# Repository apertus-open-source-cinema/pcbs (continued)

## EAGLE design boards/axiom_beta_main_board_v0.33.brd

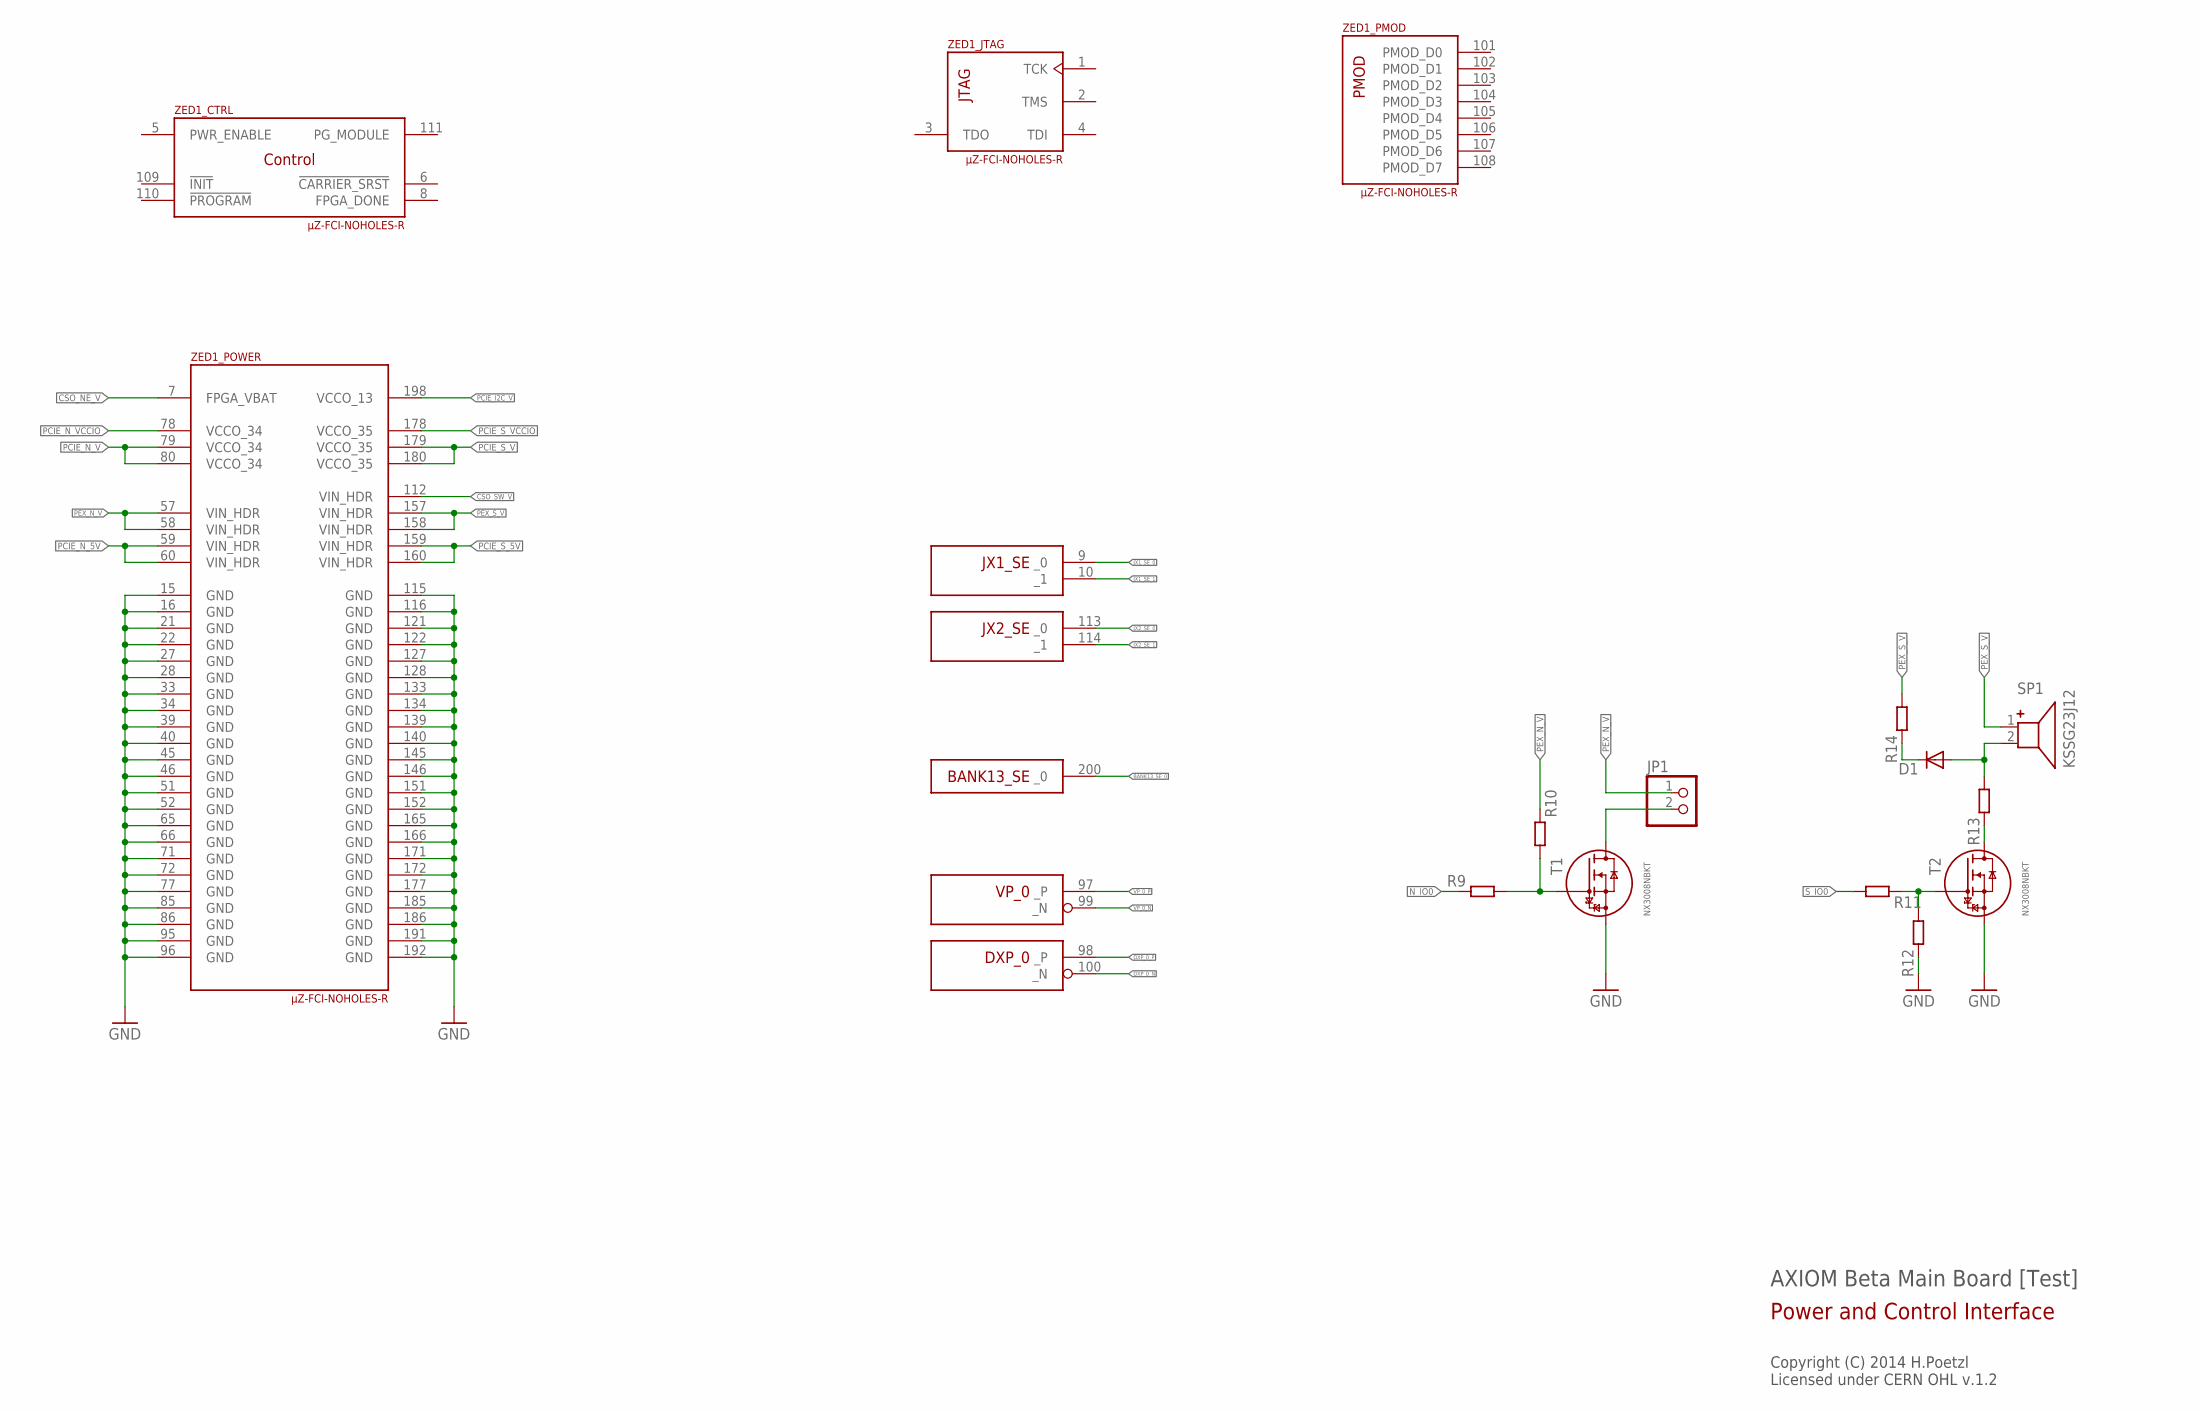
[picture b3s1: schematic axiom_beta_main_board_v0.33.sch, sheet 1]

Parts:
D1: DIODE-MICROMELF-R; MICROMELF-R
JP1: PINHD-1X02_2.00; 1X02M
R9, R10, R11, R12, R13, R14: R0402-B; 0402-B
SP1: KSSG23J12
T1, T2: NX3008NBKT; SOT416
ZED1: µZ-FCI-NOHOLES-R; µZ-NOHOLES-R

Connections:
BANK13_SE_0: ZED1.200 (_0); also elsewhere on the board
CSO_NE_V: ZED1.7 (FPGA_VBAT); also elsewhere on the board
CSO_SW_V: ZED1.112 (VIN_HDR); also elsewhere on the board
DXP_0_N: ZED1.100 (_N)
DXP_0_P: ZED1.98 (_P)
GND: R12.1, T1.2 (S), ZED1.15 (GND), ZED1.16 (GND), ZED1.21 (GND), ZED1.22 (GND), ZED1.27 (GND), ZED1.28 (GND), ZED1.33 (GND), ZED1.34 (GND), ZED1.39 (GND), ZED1.40 (GND), ZED1.45 (GND), ZED1.46 (GND), ZED1.51 (GND), ZED1.52 (GND), ZED1.65 (GND), ZED1.66 (GND), ZED1.71 (GND), ZED1.72 (GND), ZED1.77 (GND), ZED1.85 (GND), ZED1.86 (GND), ZED1.95 (GND), ZED1.96 (GND), ZED1.115 (GND), ZED1.116 (GND), ZED1.121 (GND), ZED1.122 (GND), ZED1.127 (GND), ZED1.128 (GND), ZED1.133 (GND), ZED1.134 (GND), ZED1.139 (GND), ZED1.140 (GND), ZED1.145 (GND), ZED1.146 (GND), ZED1.151 (GND), ZED1.152 (GND), ZED1.165 (GND), ZED1.166 (GND), ZED1.171 (GND), ZED1.172 (GND), ZED1.177 (GND), ZED1.185 (GND), ZED1.186 (GND), ZED1.191 (GND), ZED1.192 (GND); also elsewhere on the board
JX1_SE_0: ZED1.9 (_0); also elsewhere on the board
JX1_SE_1: ZED1.10 (_1)
JX2_SE_0: ZED1.113 (_0)
JX2_SE_1: ZED1.114 (_1)
unnamed: JP1.2, T1.3 (D)
unnamed: R13.1, T2.3 (D)
unnamed: D1.C, R14.1
unnamed: D1.A, R13.2, SP1.2
unnamed: R9.2, R10.2, T1.1 (G)
unnamed: R11.1, R12.2, T2.1 (G)
N_IO0: R9.1; also elsewhere on the board
PCIE_I2C_V: ZED1.198 (VCCO_13); also elsewhere on the board
PCIE_N_5V: ZED1.59 (VIN_HDR), ZED1.60 (VIN_HDR); also elsewhere on the board
PCIE_N_V: ZED1.79 (VCCO_34), ZED1.80 (VCCO_34); also elsewhere on the board
PCIE_N_VCCIO: ZED1.78 (VCCO_34); also elsewhere on the board
PCIE_S_5V: ZED1.159 (VIN_HDR), ZED1.160 (VIN_HDR); also elsewhere on the board
PCIE_S_V: ZED1.179 (VCCO_35), ZED1.180 (VCCO_35); also elsewhere on the board
PCIE_S_VCCIO: ZED1.178 (VCCO_35); also elsewhere on the board
PEX_N_V: JP1.1, R10.1, ZED1.57 (VIN_HDR), ZED1.58 (VIN_HDR)
PEX_S_V: R14.2, SP1.1, ZED1.157 (VIN_HDR), ZED1.158 (VIN_HDR)
S_IO0: R11.2; also elsewhere on the board
VP_0_N: ZED1.99 (_N)
VP_0_P: ZED1.97 (_P)

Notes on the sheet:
AXIOM Beta Main Board [Test]
Copyright (C) 2014 H.Poetzl Licensed under CERN OHL v.1.2
Power and Control Interface

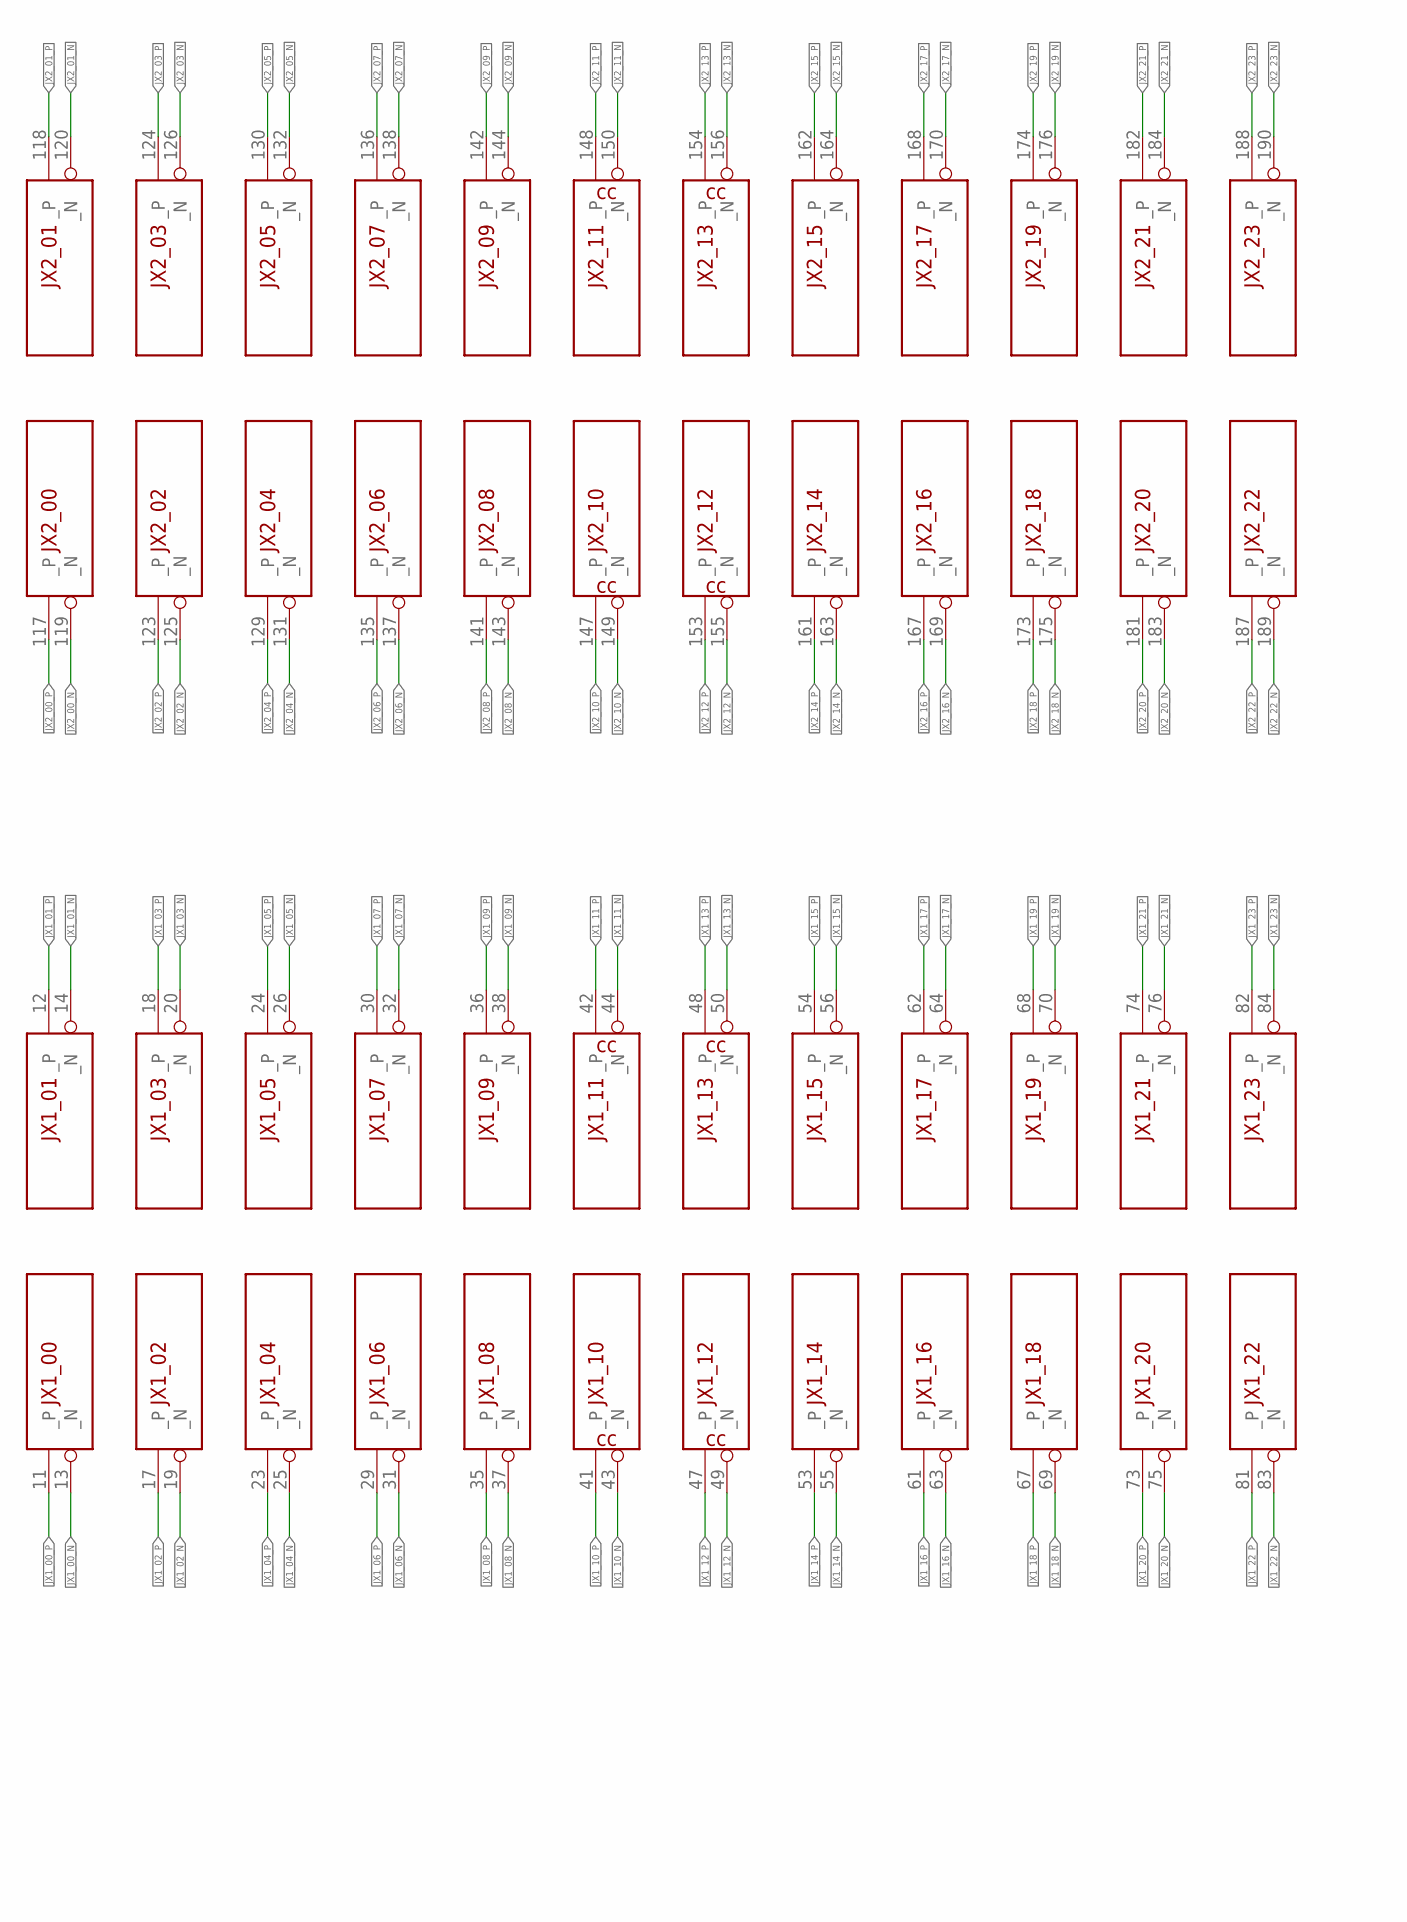
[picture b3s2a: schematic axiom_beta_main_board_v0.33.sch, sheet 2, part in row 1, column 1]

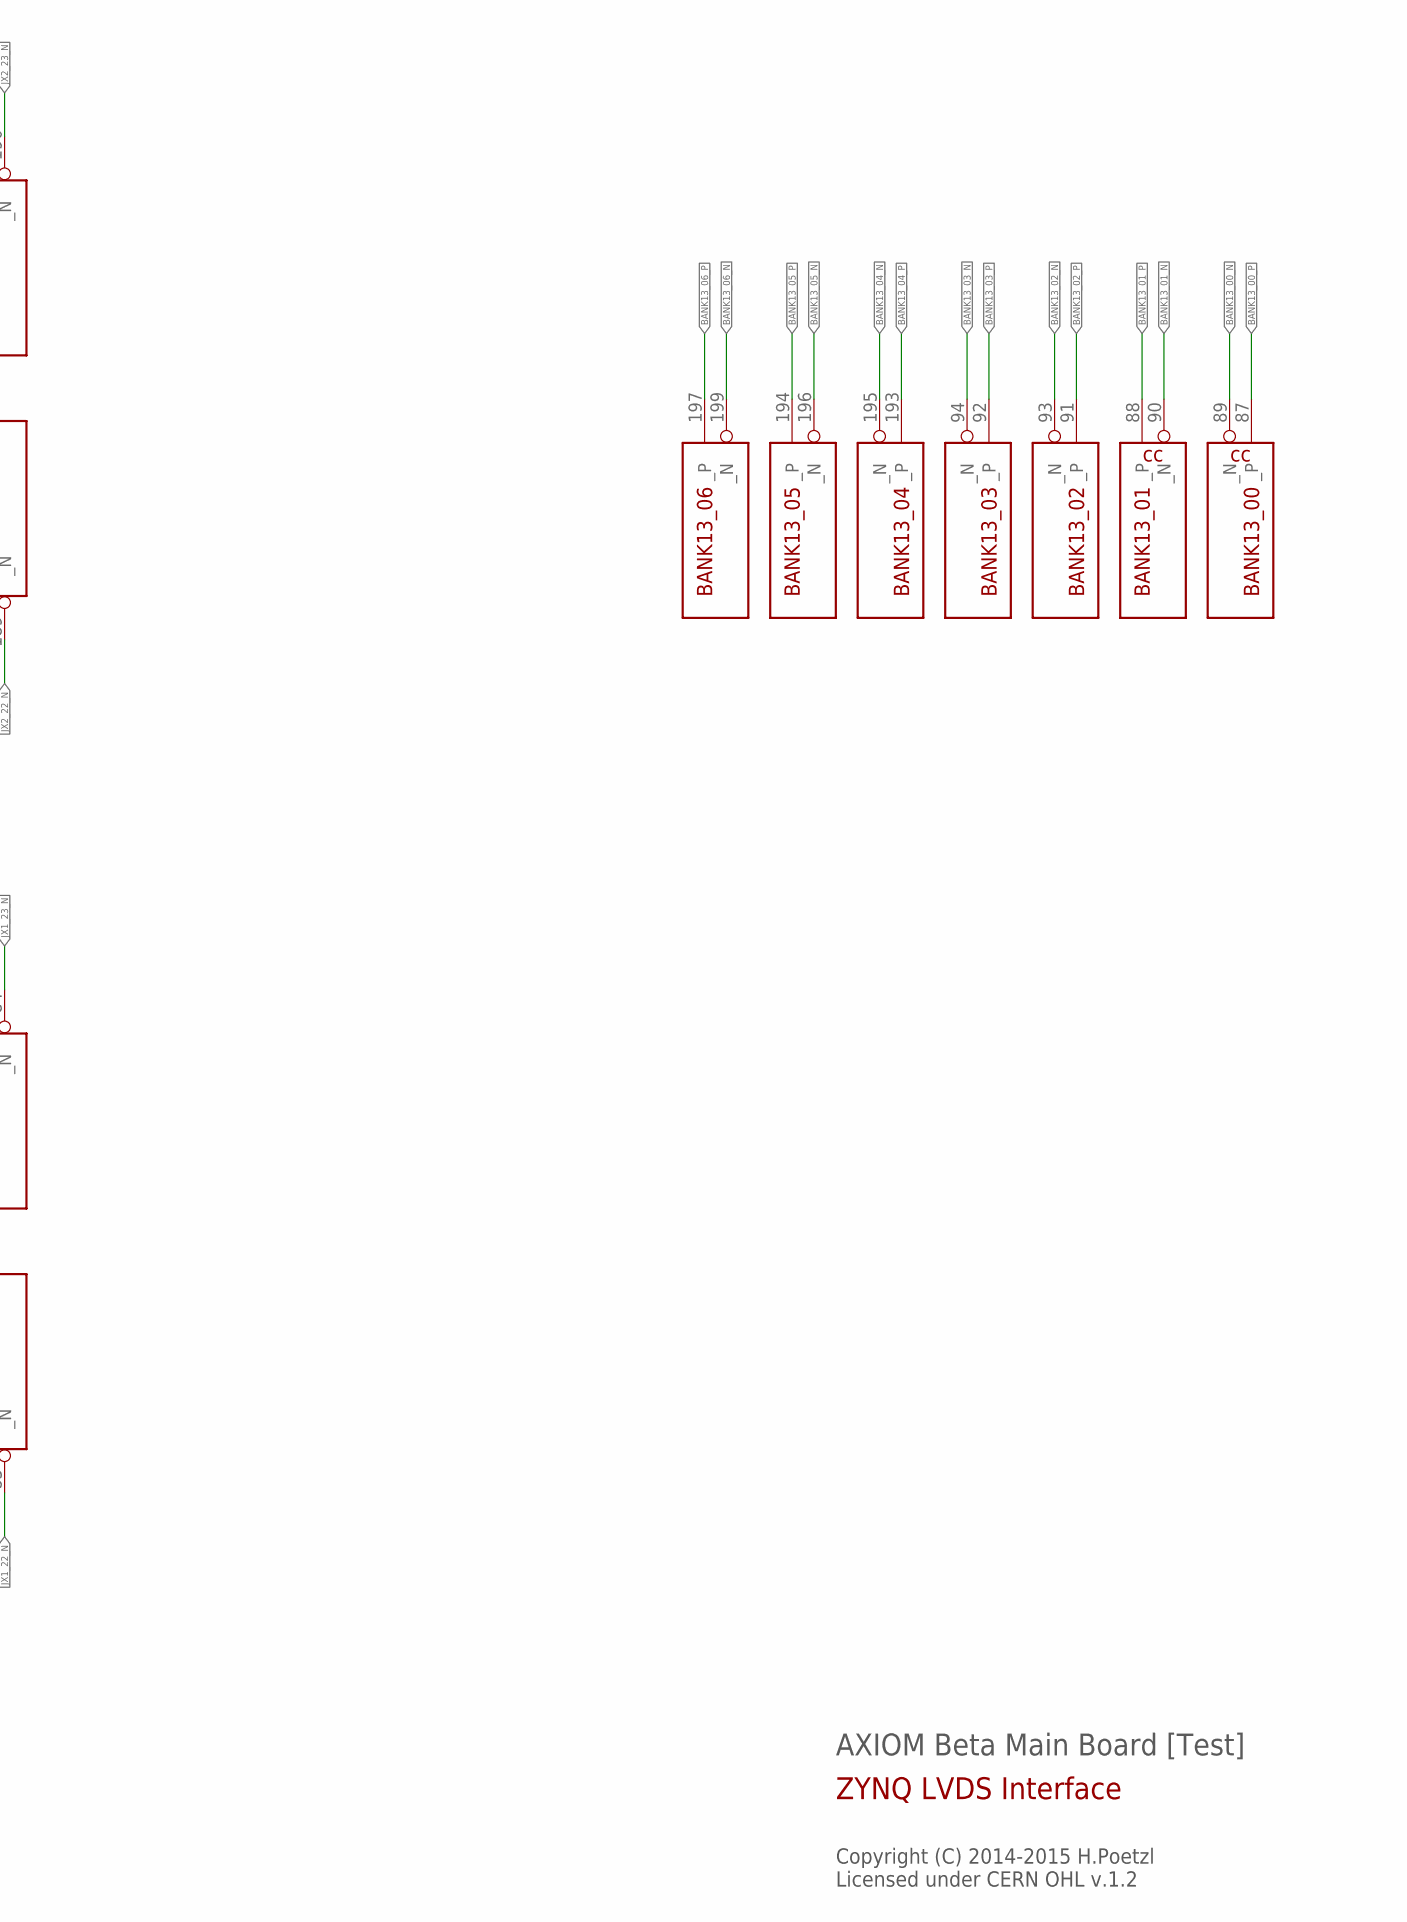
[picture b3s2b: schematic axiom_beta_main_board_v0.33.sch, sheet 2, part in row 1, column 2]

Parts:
ZED1: µZ-FCI-NOHOLES-R; µZ-NOHOLES-R

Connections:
BANK13_00_N: ZED1.89 (_N); also elsewhere on the board
BANK13_00_P: ZED1.87 (_P); also elsewhere on the board
BANK13_01_N: ZED1.90 (_N); also elsewhere on the board
BANK13_01_P: ZED1.88 (_P); also elsewhere on the board
BANK13_02_N: ZED1.93 (_N); also elsewhere on the board
BANK13_02_P: ZED1.91 (_P); also elsewhere on the board
BANK13_03_N: ZED1.94 (_N); also elsewhere on the board
BANK13_03_P: ZED1.92 (_P); also elsewhere on the board
BANK13_04_N: ZED1.195 (_N); also elsewhere on the board
BANK13_04_P: ZED1.193 (_P); also elsewhere on the board
BANK13_05_N: ZED1.196 (_N); also elsewhere on the board
BANK13_05_P: ZED1.194 (_P); also elsewhere on the board
BANK13_06_N: ZED1.199 (_N); also elsewhere on the board
BANK13_06_P: ZED1.197 (_P); also elsewhere on the board
JX1_00_N: ZED1.13 (_N); also elsewhere on the board
JX1_00_P: ZED1.11 (_P); also elsewhere on the board
JX1_01_N: ZED1.14 (_N); also elsewhere on the board
JX1_01_P: ZED1.12 (_P); also elsewhere on the board
JX1_02_N: ZED1.19 (_N); also elsewhere on the board
JX1_02_P: ZED1.17 (_P); also elsewhere on the board
JX1_03_N: ZED1.20 (_N); also elsewhere on the board
JX1_03_P: ZED1.18 (_P); also elsewhere on the board
JX1_04_N: ZED1.25 (_N); also elsewhere on the board
JX1_04_P: ZED1.23 (_P); also elsewhere on the board
JX1_05_N: ZED1.26 (_N); also elsewhere on the board
JX1_05_P: ZED1.24 (_P); also elsewhere on the board
JX1_06_N: ZED1.31 (_N); also elsewhere on the board
JX1_06_P: ZED1.29 (_P); also elsewhere on the board
JX1_07_N: ZED1.32 (_N); also elsewhere on the board
JX1_07_P: ZED1.30 (_P); also elsewhere on the board
JX1_08_N: ZED1.37 (_N); also elsewhere on the board
JX1_08_P: ZED1.35 (_P); also elsewhere on the board
JX1_09_N: ZED1.38 (_N); also elsewhere on the board
JX1_09_P: ZED1.36 (_P); also elsewhere on the board
JX1_10_N: ZED1.43 (_N); also elsewhere on the board
JX1_10_P: ZED1.41 (_P); also elsewhere on the board
JX1_11_N: ZED1.44 (_N); also elsewhere on the board
JX1_11_P: ZED1.42 (_P); also elsewhere on the board
JX1_12_N: ZED1.49 (_N); also elsewhere on the board
JX1_12_P: ZED1.47 (_P); also elsewhere on the board
JX1_13_N: ZED1.50 (_N); also elsewhere on the board
JX1_13_P: ZED1.48 (_P); also elsewhere on the board
JX1_14_N: ZED1.55 (_N); also elsewhere on the board
JX1_14_P: ZED1.53 (_P); also elsewhere on the board
JX1_15_N: ZED1.56 (_N); also elsewhere on the board
JX1_15_P: ZED1.54 (_P); also elsewhere on the board
JX1_16_N: ZED1.63 (_N); also elsewhere on the board
JX1_16_P: ZED1.61 (_P); also elsewhere on the board
JX1_17_N: ZED1.64 (_N); also elsewhere on the board
JX1_17_P: ZED1.62 (_P); also elsewhere on the board
JX1_18_N: ZED1.69 (_N); also elsewhere on the board
JX1_18_P: ZED1.67 (_P); also elsewhere on the board
JX1_19_N: ZED1.70 (_N); also elsewhere on the board
JX1_19_P: ZED1.68 (_P); also elsewhere on the board
JX1_20_N: ZED1.75 (_N); also elsewhere on the board
JX1_20_P: ZED1.73 (_P); also elsewhere on the board
JX1_21_N: ZED1.76 (_N); also elsewhere on the board
JX1_21_P: ZED1.74 (_P); also elsewhere on the board
JX1_22_N: ZED1.83 (_N); also elsewhere on the board
JX1_22_P: ZED1.81 (_P); also elsewhere on the board
JX1_23_N: ZED1.84 (_N); also elsewhere on the board
JX1_23_P: ZED1.82 (_P); also elsewhere on the board
JX2_00_N: ZED1.119 (_N); also elsewhere on the board
JX2_00_P: ZED1.117 (_P); also elsewhere on the board
JX2_01_N: ZED1.120 (_N); also elsewhere on the board
JX2_01_P: ZED1.118 (_P); also elsewhere on the board
JX2_02_N: ZED1.125 (_N); also elsewhere on the board
JX2_02_P: ZED1.123 (_P); also elsewhere on the board
JX2_03_N: ZED1.126 (_N); also elsewhere on the board
JX2_03_P: ZED1.124 (_P); also elsewhere on the board
JX2_04_N: ZED1.131 (_N); also elsewhere on the board
JX2_04_P: ZED1.129 (_P); also elsewhere on the board
JX2_05_N: ZED1.132 (_N); also elsewhere on the board
JX2_05_P: ZED1.130 (_P); also elsewhere on the board
JX2_06_N: ZED1.137 (_N); also elsewhere on the board
JX2_06_P: ZED1.135 (_P); also elsewhere on the board
JX2_07_N: ZED1.138 (_N); also elsewhere on the board
JX2_07_P: ZED1.136 (_P); also elsewhere on the board
JX2_08_N: ZED1.143 (_N); also elsewhere on the board
JX2_08_P: ZED1.141 (_P); also elsewhere on the board
JX2_09_N: ZED1.144 (_N); also elsewhere on the board
JX2_09_P: ZED1.142 (_P); also elsewhere on the board
JX2_10_N: ZED1.149 (_N); also elsewhere on the board
JX2_10_P: ZED1.147 (_P); also elsewhere on the board
JX2_11_N: ZED1.150 (_N); also elsewhere on the board
JX2_11_P: ZED1.148 (_P); also elsewhere on the board
JX2_12_N: ZED1.155 (_N); also elsewhere on the board
JX2_12_P: ZED1.153 (_P); also elsewhere on the board
JX2_13_N: ZED1.156 (_N); also elsewhere on the board
JX2_13_P: ZED1.154 (_P); also elsewhere on the board
JX2_14_N: ZED1.163 (_N); also elsewhere on the board
JX2_14_P: ZED1.161 (_P); also elsewhere on the board
JX2_15_N: ZED1.164 (_N); also elsewhere on the board
JX2_15_P: ZED1.162 (_P); also elsewhere on the board
JX2_16_N: ZED1.169 (_N); also elsewhere on the board
JX2_16_P: ZED1.167 (_P); also elsewhere on the board
JX2_17_N: ZED1.170 (_N); also elsewhere on the board
JX2_17_P: ZED1.168 (_P); also elsewhere on the board
JX2_18_N: ZED1.175 (_N); also elsewhere on the board
JX2_18_P: ZED1.173 (_P); also elsewhere on the board
JX2_19_N: ZED1.176 (_N); also elsewhere on the board
JX2_19_P: ZED1.174 (_P); also elsewhere on the board
JX2_20_N: ZED1.183 (_N); also elsewhere on the board
JX2_20_P: ZED1.181 (_P); also elsewhere on the board
JX2_21_N: ZED1.184 (_N); also elsewhere on the board
JX2_21_P: ZED1.182 (_P); also elsewhere on the board
JX2_22_N: ZED1.189 (_N); also elsewhere on the board
JX2_22_P: ZED1.187 (_P); also elsewhere on the board
JX2_23_N: ZED1.190 (_N); also elsewhere on the board
JX2_23_P: ZED1.188 (_P); also elsewhere on the board

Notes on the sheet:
AXIOM Beta Main Board [Test]
Copyright (C) 2014-2015 H.Poetzl Licensed under CERN OHL v.1.2
ZYNQ LVDS Interface
